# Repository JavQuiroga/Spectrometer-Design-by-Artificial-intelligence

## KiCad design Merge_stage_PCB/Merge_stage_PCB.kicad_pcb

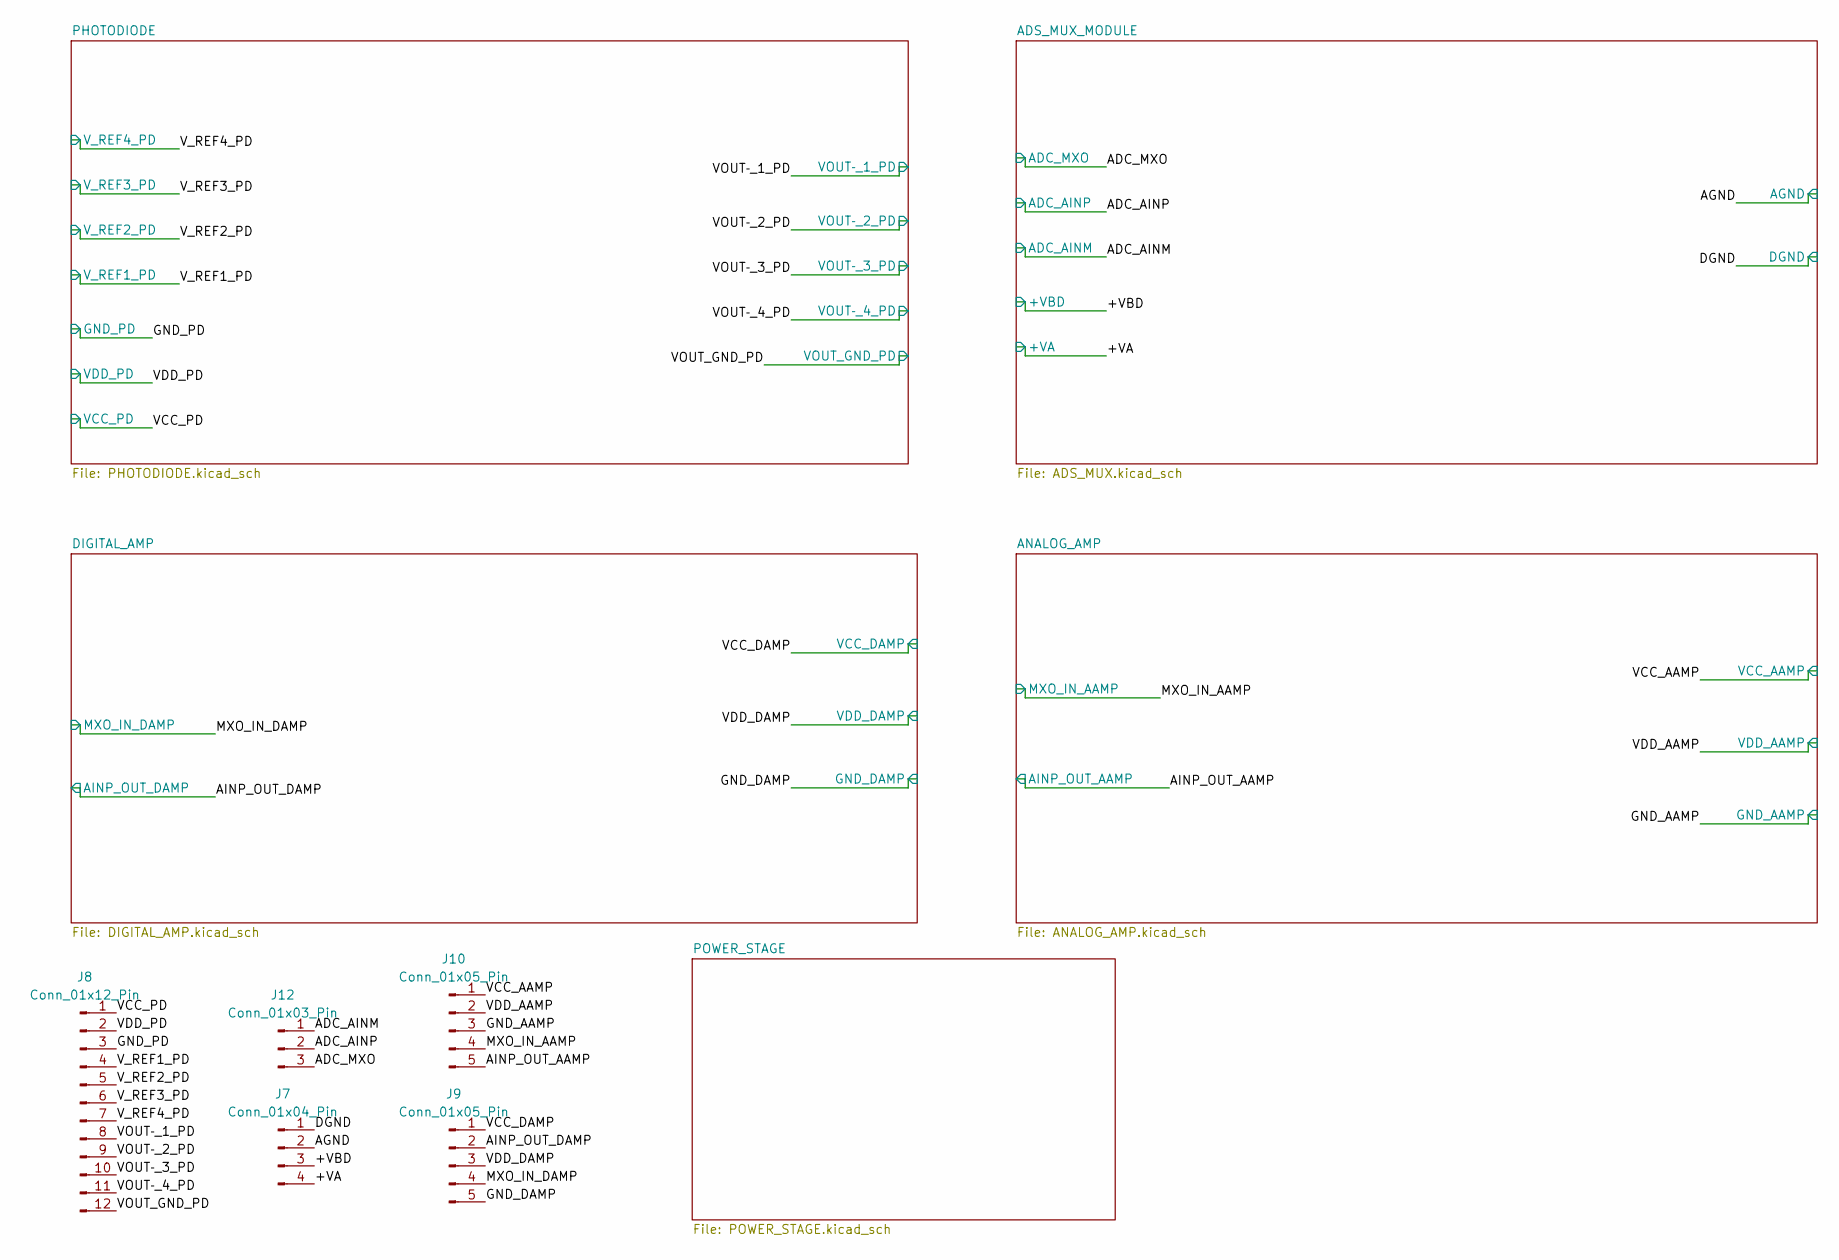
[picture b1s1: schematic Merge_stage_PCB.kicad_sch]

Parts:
J7: Conn_01x04_Pin; PinHeader_1x04_P2.54mm_Vertical
J8: Conn_01x12_Pin; PinHeader_1x12_P2.54mm_Vertical
J9, J10: Conn_01x05_Pin; PinHeader_1x05_P2.54mm_Vertical
J12: Conn_01x03_Pin; PinHeader_1x03_P2.54mm_Vertical

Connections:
+3.3V: J7.3; also elsewhere on the board
+5V: J7.4; also elsewhere on the board
/ADC_AINM: J12.1; also elsewhere on the board
/ADC_AINP: J12.2; also elsewhere on the board
/ADC_MXO: J12.3; also elsewhere on the board
/AGND: J7.2; also elsewhere on the board
/AINP_OUT_AAMP: J10.5; also elsewhere on the board
/AINP_OUT_DAMP: J9.2; also elsewhere on the board
/DGND: J7.1; also elsewhere on the board
/MXO_IN_AAMP: J10.4; also elsewhere on the board
/MXO_IN_DAMP: J9.4; also elsewhere on the board
/VCC_AAMP: J10.1; also elsewhere on the board
/VCC_DAMP: J9.1; also elsewhere on the board
/VCC_PD: J8.1; also elsewhere on the board
/VDD_AAMP: J10.2; also elsewhere on the board
/VDD_DAMP: J9.3; also elsewhere on the board
/VDD_PD: J8.2; also elsewhere on the board
/VOUT­_1_PD: J8.8; also elsewhere on the board
/VOUT­_2_PD: J8.9; also elsewhere on the board
/VOUT­_3_PD: J8.10; also elsewhere on the board
/VOUT­_4_PD: J8.11; also elsewhere on the board
/V_REF1_PD: J8.4; also elsewhere on the board
/V_REF2_PD: J8.5; also elsewhere on the board
/V_REF3_PD: J8.6; also elsewhere on the board
/V_REF4_PD: J8.7; also elsewhere on the board
GND_AAMP: J10.3; also elsewhere on the board
GND_DAMP: J9.5; also elsewhere on the board
GND_PD: J8.3, J8.12; also elsewhere on the board

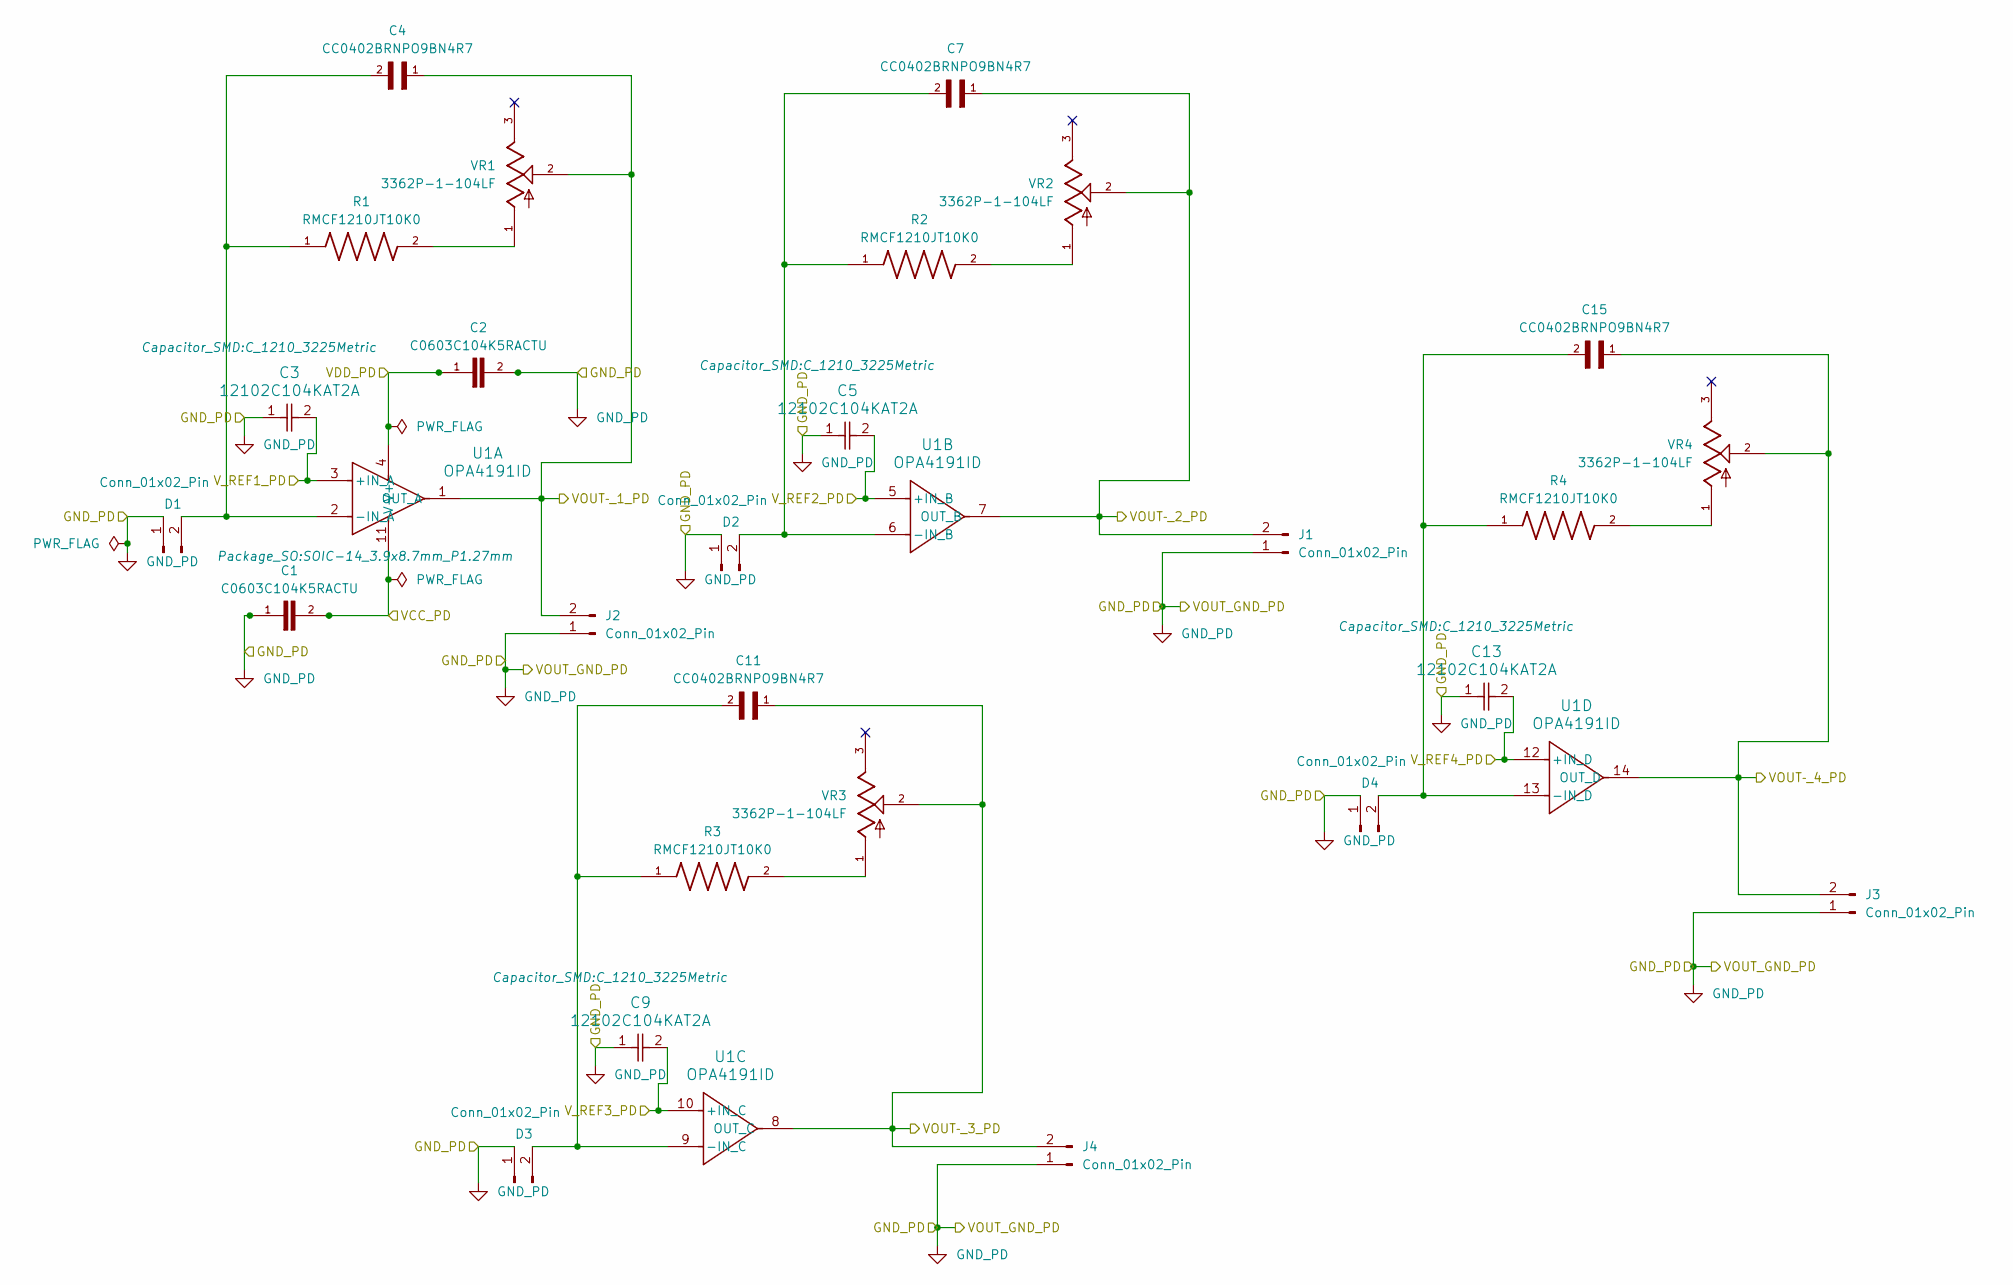
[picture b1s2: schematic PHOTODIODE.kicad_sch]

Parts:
C1, C2: C0603C104K5RACTU; C_0603_1608Metric
C3, C5, C9, C13: 12102C104KAT2A; C_1210_3225Metric
C4, C7, C15: CC0402BRNPO9BN4R7; C_0402_1005Metric
C11: CC0402BRNPO9BN4R7; C_0402_1005Metric_Pad0.74x0.62mm_HandSolder
D1, D2, D3, D4: Conn_01x02_Pin; PinHeader_1x02_P2.00mm_Vertical
J1, J2, J3, J4: Conn_01x02_Pin; PinHeader_1x02_P2.54mm_Vertical
R1, R2, R3, R4: RMCF1210JT10K0; R_1210_3225Metric
U1: OPA4191ID; SOIC-14_3.9x8.7mm_P1.27mm
VR1, VR2, VR3, VR4: 3362P-1-104LF; TRIM_3362P-1-104LF; PARTREV 08/26/10

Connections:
/VCC_PD: C1.2, U1.11 (V-); also elsewhere on the board
/VDD_PD: C2.1, U1.4 (V+); also elsewhere on the board
/VOUT­_1_PD: C4.1, J2.2, U1.1 (OUT_A), VR1.2; also elsewhere on the board
/VOUT­_2_PD: C7.1, J1.2, U1.7 (OUT_B), VR2.2; also elsewhere on the board
/VOUT­_3_PD: C11.1, J4.2, U1.8 (OUT_C), VR3.2; also elsewhere on the board
/VOUT­_4_PD: C15.1, J3.2, U1.14 (OUT_D), VR4.2; also elsewhere on the board
/V_REF1_PD: C3.2, U1.3 (+IN_A); also elsewhere on the board
/V_REF2_PD: C5.2, U1.5 (+IN_B); also elsewhere on the board
/V_REF3_PD: C9.2, U1.10 (+IN_C); also elsewhere on the board
/V_REF4_PD: C13.2, U1.12 (+IN_D); also elsewhere on the board
GND_PD: C1.1, C2.2, C3.1, C5.1, C9.1, C13.1, D1.1, D2.1, D3.1, D4.1, J1.1, J2.1, J3.1, J4.1; also elsewhere on the board
unnamed: C4.2, D1.2, R1.1, U1.2 (-IN_A)
unnamed: C7.2, D2.2, R2.1, U1.6 (-IN_B)
unnamed: C11.2, D3.2, R3.1, U1.9 (-IN_C)
unnamed: C15.2, D4.2, R4.1, U1.13 (-IN_D)
unnamed: R1.2, VR1.1
unnamed: R2.2, VR2.1
unnamed: R3.2, VR3.1
unnamed: R4.2, VR4.1

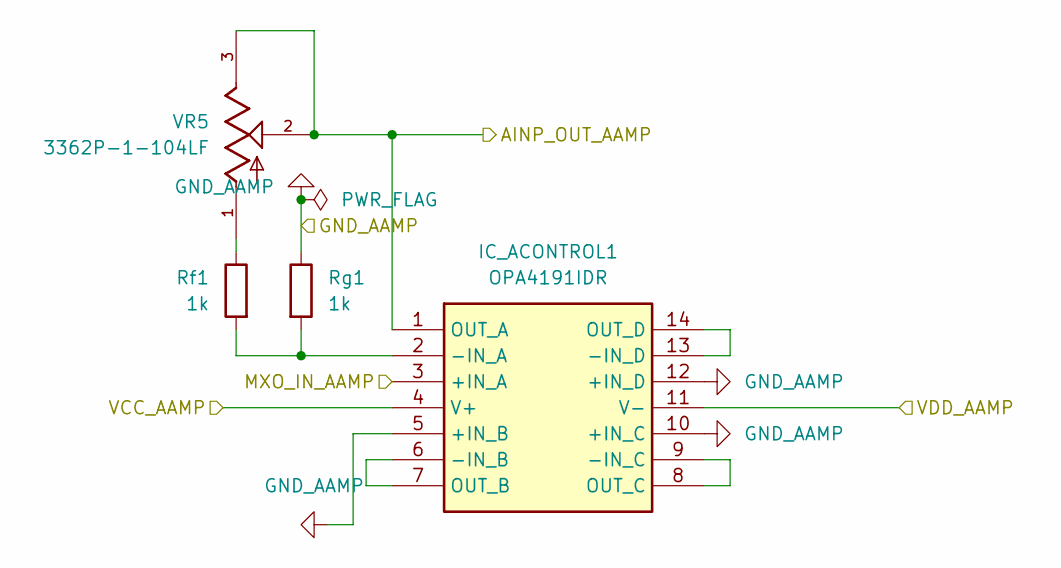
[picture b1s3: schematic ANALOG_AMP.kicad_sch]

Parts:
IC_ACONTROL1: OPA4191IDR; SOIC127P600X175-14N; Mouser Part Number 595-OPA4191IDR
Rf1: 1k; R_1210_3225Metric
Rg1: 1k; R_1210_3225Metric
VR5: 3362P-1-104LF; TRIM_3362P-1-104LF; PARTREV 08/26/10

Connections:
/AINP_OUT_AAMP: IC_ACONTROL1.1 (OUT_A), VR5.2, VR5.3; also elsewhere on the board
GND_AAMP: IC_ACONTROL1.5 (+IN_B), IC_ACONTROL1.10 (+IN_C), IC_ACONTROL1.12 (+IN_D), Rg1.1; also elsewhere on the board
unnamed 65: IC_ACONTROL1.2 (-IN_A), Rf1.2, Rg1.2; also elsewhere on the board
unnamed: IC_ACONTROL1.6 (-IN_B), IC_ACONTROL1.7 (OUT_B)
unnamed: IC_ACONTROL1.8 (OUT_C), IC_ACONTROL1.9 (-IN_C)
unnamed: IC_ACONTROL1.13 (-IN_D), IC_ACONTROL1.14 (OUT_D)
unnamed: Rf1.1, VR5.1

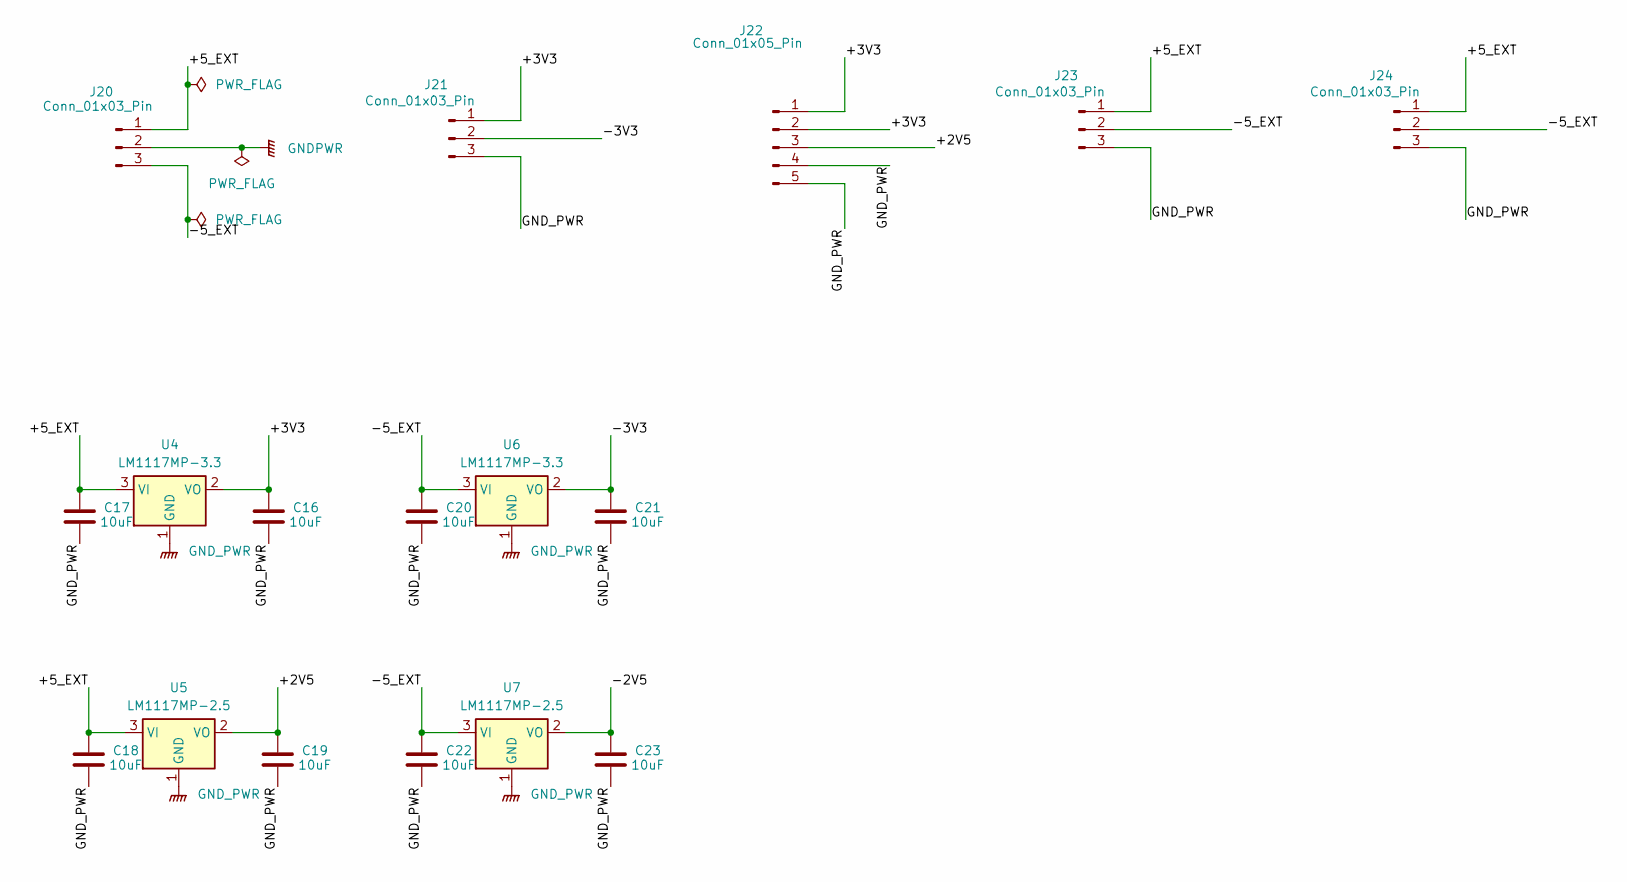
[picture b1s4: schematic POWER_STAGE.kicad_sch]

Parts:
C16, C17, C18, C19, C20, C21, C22, C23: 10uF; C_0805_2012Metric
J20, J21, J23, J24: Conn_01x03_Pin; PinHeader_1x03_P2.54mm_Vertical
J22: Conn_01x05_Pin; PinHeader_1x05_P2.54mm_Vertical
U4, U6: LM1117MP-3.3; SOT-223-3_TabPin2
U5, U7: LM1117MP-2.5; SOT-223-3_TabPin2

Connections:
/POWER_STAGE/+2V5: C19.1, J22.3, U5.2 (VO)
/POWER_STAGE/+3V3: C16.1, J21.1, J22.1, J22.2, U4.2 (VO)
/POWER_STAGE/+5_EXT: C17.1, C18.1, J20.1, J23.1, J24.1, U4.3 (VI), U5.3 (VI)
/POWER_STAGE/-2V5: C23.1, U7.2 (VO)
/POWER_STAGE/-3V3: C21.1, J21.2, U6.2 (VO)
/POWER_STAGE/-5_EXT: C20.1, C22.1, J20.3, J23.2, J24.2, U6.3 (VI), U7.3 (VI)
GNDPWR: J20.2
GND_PWR: C16.2, C17.2, C18.2, C19.2, C20.2, C21.2, C22.2, C23.2, J21.3, J22.4, J22.5, J23.3, J24.3, U4.1 (GND), U5.1 (GND), U6.1 (GND), U7.1 (GND)

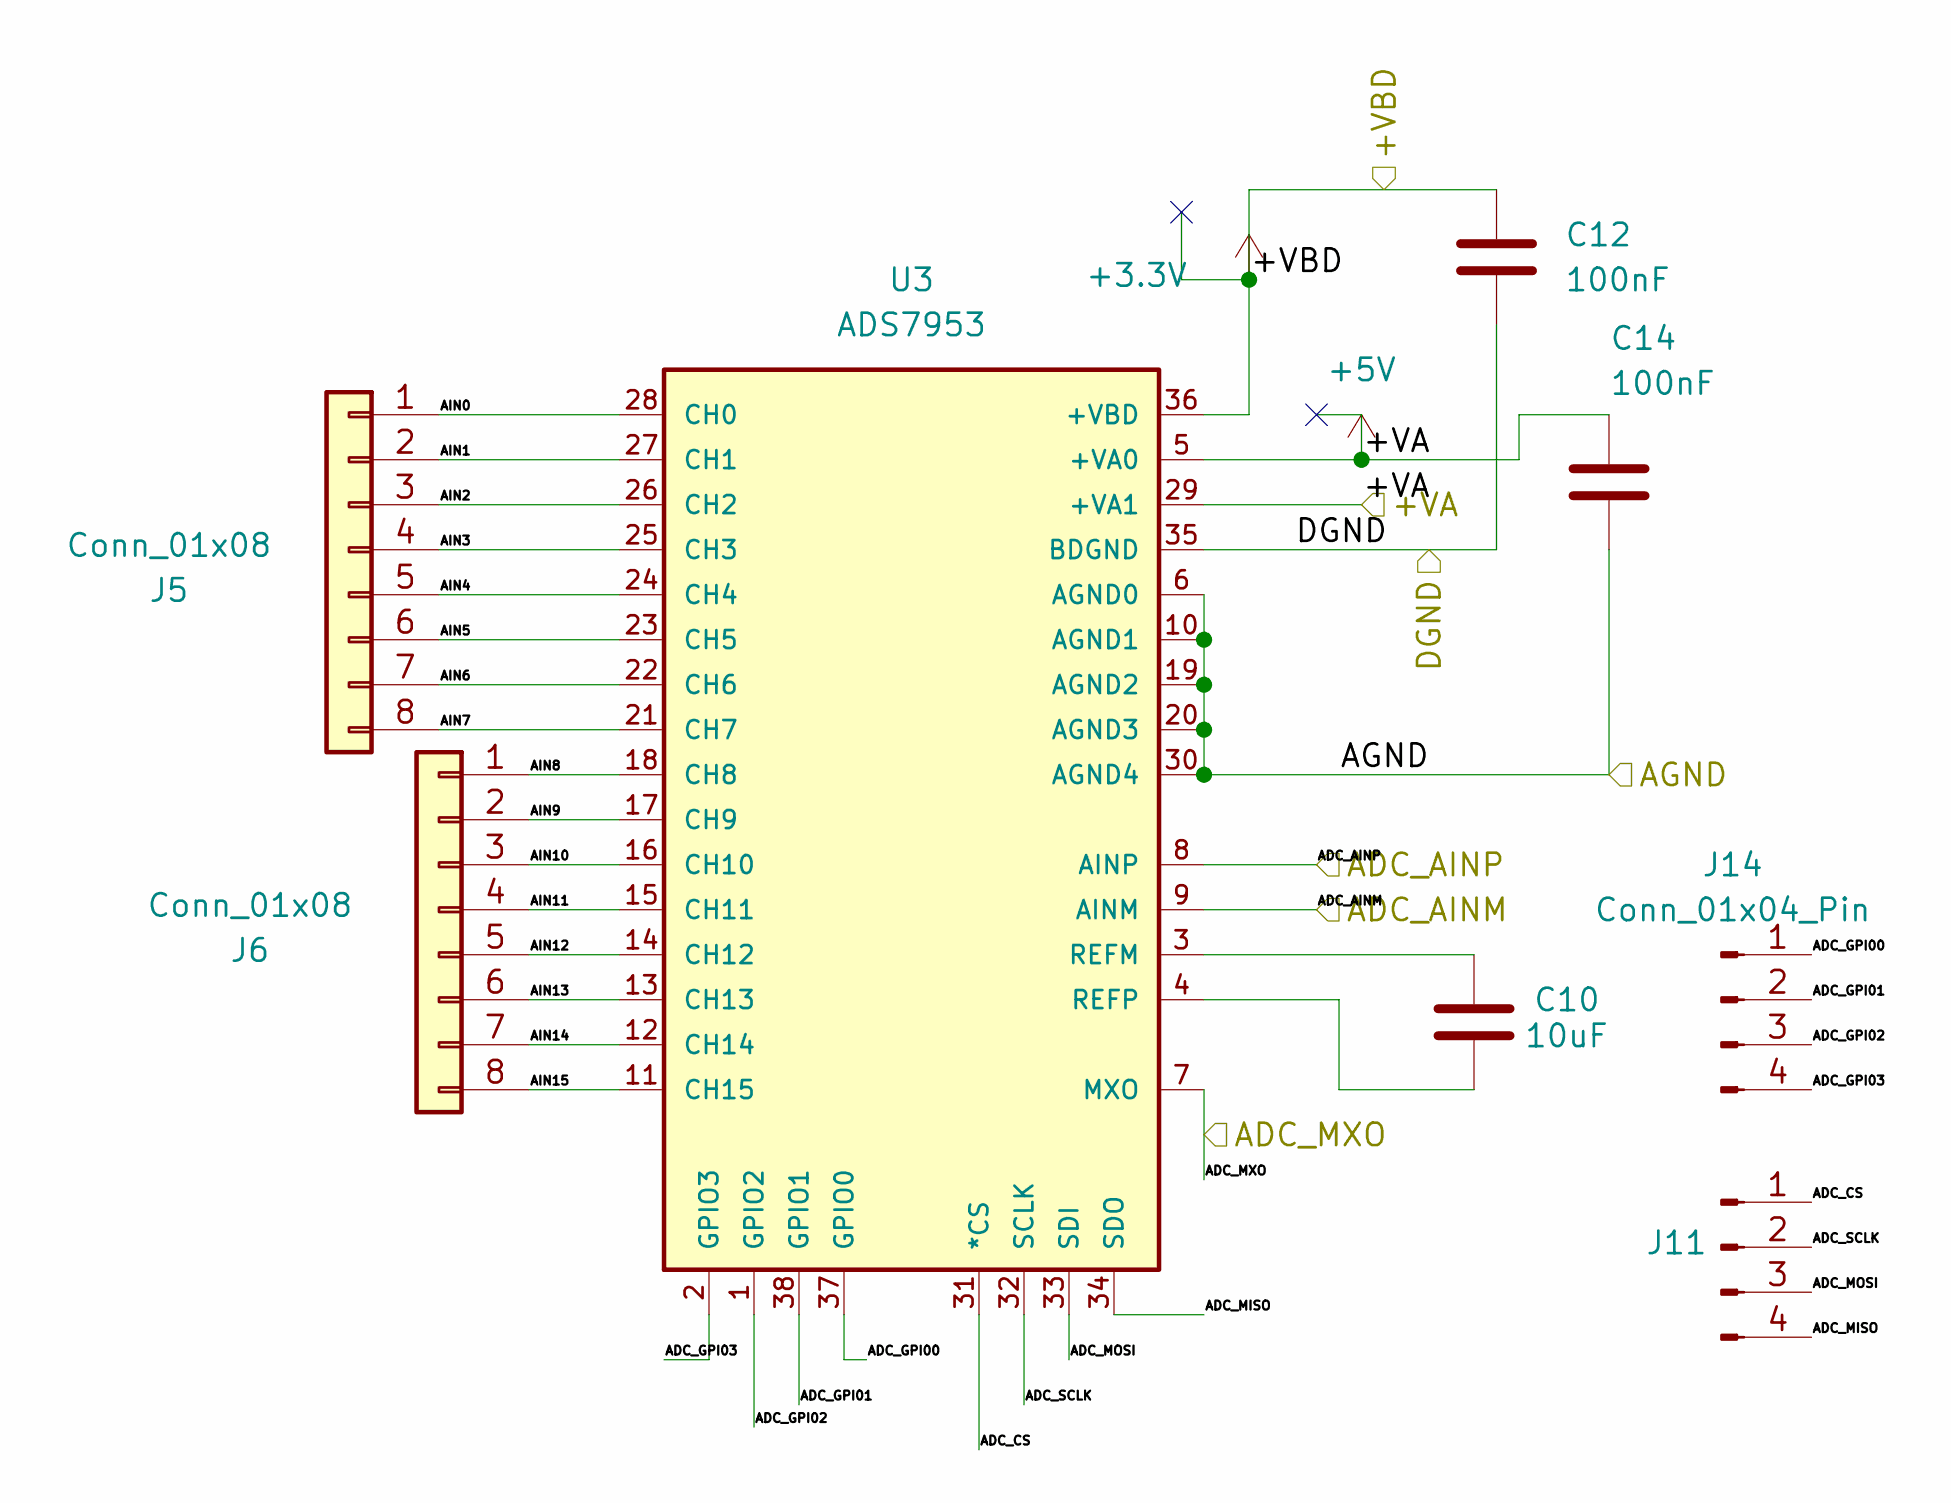
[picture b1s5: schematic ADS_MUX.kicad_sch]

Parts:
C10: 10uF; C_0805_2012Metric
C12, C14: 100nF; C_0805_2012Metric
J5, J6: Conn_01x08; PinHeader_1x08_P2.54mm_Vertical
J11, J14: Conn_01x04_Pin; PinHeader_1x04_P2.54mm_Vertical
U3: ADS7953

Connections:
+3.3V: C12.1, U3.36 (+VBD); also elsewhere on the board
+5V: C14.1, U3.5 (+VA0), U3.29 (+VA1); also elsewhere on the board
/ADC_AINM: U3.9 (AINM); also elsewhere on the board
/ADC_AINP: U3.8 (AINP); also elsewhere on the board
/ADC_MXO: U3.7 (MXO); also elsewhere on the board
/ADS_MUX_MODULE/ADC_CS: J11.1, U3.31 (*CS)
/ADS_MUX_MODULE/ADC_GPI00: J14.1, U3.37 (GPIO0)
/ADS_MUX_MODULE/ADC_GPI01: J14.2, U3.38 (GPIO1)
/ADS_MUX_MODULE/ADC_GPI02: J14.3, U3.1 (GPIO2)
/ADS_MUX_MODULE/ADC_GPI03: J14.4, U3.2 (GPIO3)
/ADS_MUX_MODULE/ADC_MISO: J11.4, U3.34 (SDO)
/ADS_MUX_MODULE/ADC_MOSI: J11.3, U3.33 (SDI)
/ADS_MUX_MODULE/ADC_SCLK: J11.2, U3.32 (SCLK)
/ADS_MUX_MODULE/AIN0: J5.1, U3.28 (CH0)
/ADS_MUX_MODULE/AIN1: J5.2, U3.27 (CH1)
/ADS_MUX_MODULE/AIN2: J5.3, U3.26 (CH2)
/ADS_MUX_MODULE/AIN3: J5.4, U3.25 (CH3)
/ADS_MUX_MODULE/AIN4: J5.5, U3.24 (CH4)
/ADS_MUX_MODULE/AIN5: J5.6, U3.23 (CH5)
/ADS_MUX_MODULE/AIN6: J5.7, U3.22 (CH6)
/ADS_MUX_MODULE/AIN7: J5.8, U3.21 (CH7)
/ADS_MUX_MODULE/AIN8: J6.1, U3.18 (CH8)
/ADS_MUX_MODULE/AIN9: J6.2, U3.17 (CH9)
/ADS_MUX_MODULE/AIN10: J6.3, U3.16 (CH10)
/ADS_MUX_MODULE/AIN11: J6.4, U3.15 (CH11)
/ADS_MUX_MODULE/AIN12: J6.5, U3.14 (CH12)
/ADS_MUX_MODULE/AIN13: J6.6, U3.13 (CH13)
/ADS_MUX_MODULE/AIN14: J6.7, U3.12 (CH14)
/ADS_MUX_MODULE/AIN15: J6.8, U3.11 (CH15)
/AGND: C14.2, U3.6 (AGND0), U3.10 (AGND1), U3.19 (AGND2), U3.20 (AGND3), U3.30 (AGND4); also elsewhere on the board
/DGND: C12.2, U3.35 (BDGND); also elsewhere on the board
/VREF_ADC: C10.2, U3.4 (REFP)
unnamed: C10.1, U3.3 (REFM)

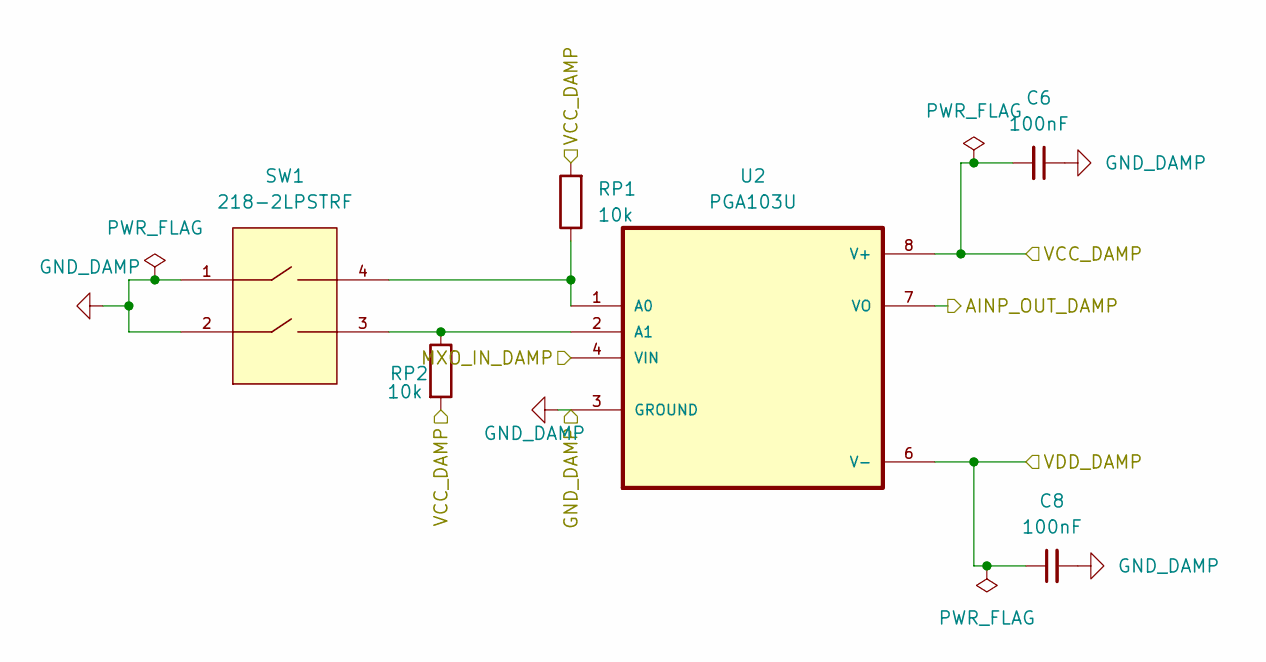
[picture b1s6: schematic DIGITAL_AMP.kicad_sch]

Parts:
C6, C8: 100nF; C_1210_3225Metric
RP1, RP2: 10k; R_1210_3225Metric
SW1: 218-2LPSTRF; SW_218-2LPSTRF; MPN 218-2LPSTRF
U2: PGA103U; SOIC127P599X175-8N

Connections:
/VCC_DAMP: C6.2, RP1.2, RP2.2, U2.8 (V+); also elsewhere on the board
/VDD_DAMP: C8.1, U2.6 (V-); also elsewhere on the board
GND_DAMP: C6.1, C8.2, SW1.1, SW1.2, U2.3 (GROUND); also elsewhere on the board
unnamed 77: RP1.1, SW1.4, U2.1 (A0); also elsewhere on the board
unnamed 78: RP2.1, SW1.3, U2.2 (A1); also elsewhere on the board

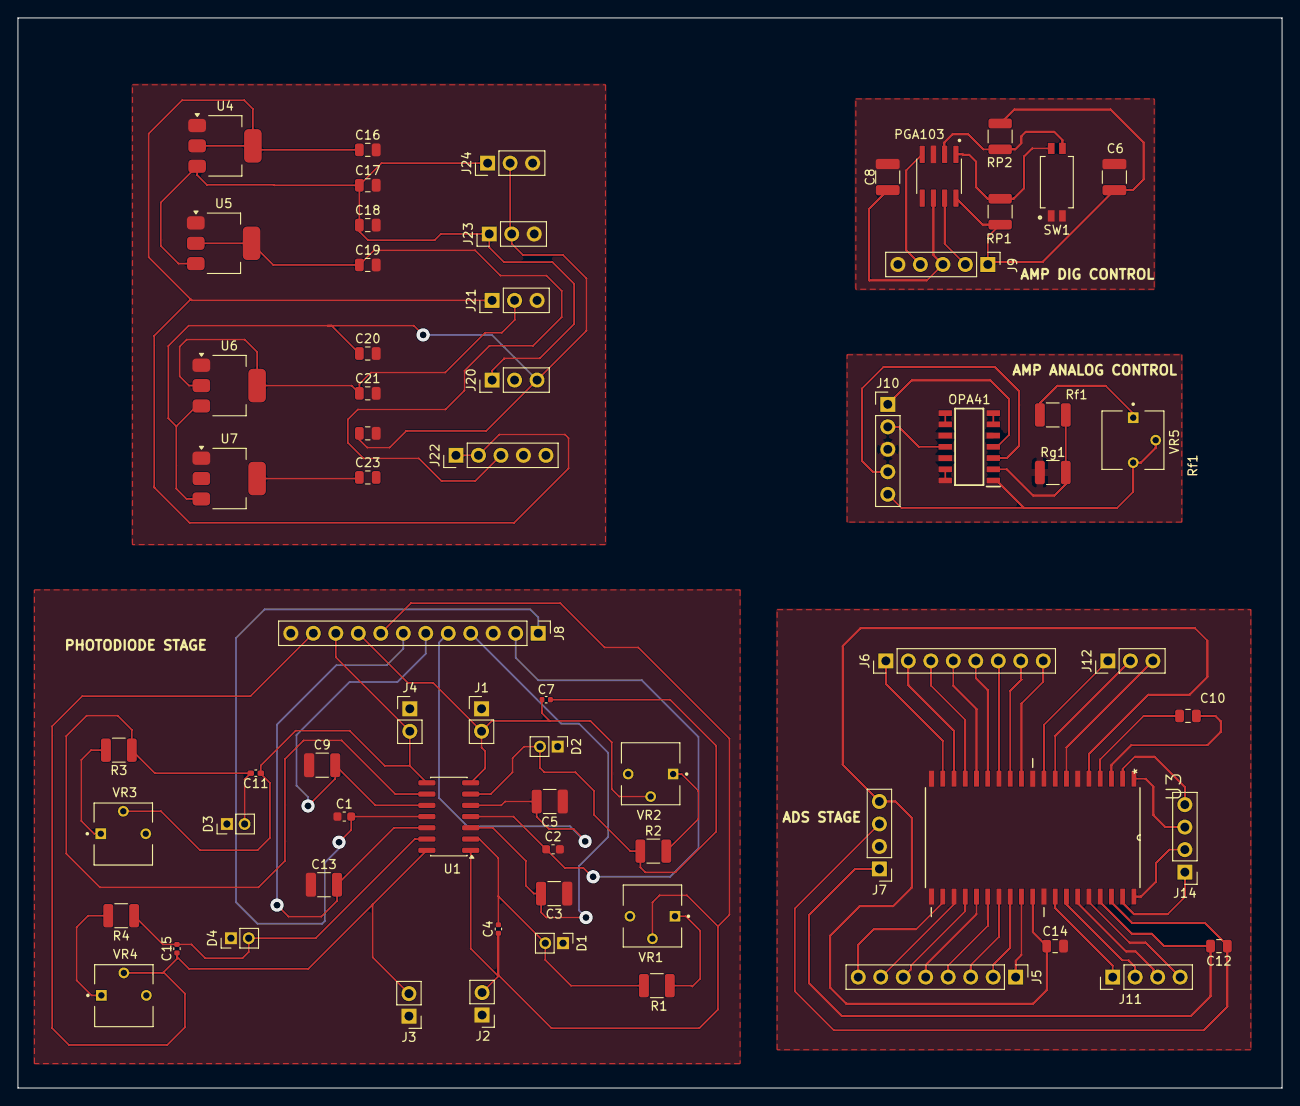
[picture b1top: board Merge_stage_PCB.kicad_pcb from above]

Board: 2 copper layers, 142.8 x 120.9 mm, 67 parts (0 on the bottom side), 76 nets.

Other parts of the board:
AMP ANALOG CONTROL: OPA4191IDR; SOIC127P600X175-14N
PGA103: PGA103U; SOIC127P599X175-8N

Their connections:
/AINP_OUT_AAMP: AMP ANALOG CONTROL.1 (OUT_A); also elsewhere on the board
/AINP_OUT_DAMP: PGA103.7 (VO); also elsewhere on the board
/MXO_IN_AAMP: AMP ANALOG CONTROL.3 (+IN_A); also elsewhere on the board
/MXO_IN_DAMP: PGA103.4 (VIN); also elsewhere on the board
/VCC_AAMP: AMP ANALOG CONTROL.4 (V+); also elsewhere on the board
/VCC_DAMP: PGA103.8 (V+); also elsewhere on the board
/VDD_AAMP: AMP ANALOG CONTROL.11 (V-); also elsewhere on the board
/VDD_DAMP: PGA103.6 (V-); also elsewhere on the board
GND_AAMP: AMP ANALOG CONTROL.5 (+IN_B), AMP ANALOG CONTROL.10 (+IN_C), AMP ANALOG CONTROL.12 (+IN_D); also elsewhere on the board
GND_DAMP: PGA103.3 (GROUND); also elsewhere on the board
unnamed 65: AMP ANALOG CONTROL.2 (-IN_A); also elsewhere on the board
unnamed: AMP ANALOG CONTROL.6 (-IN_B), AMP ANALOG CONTROL.7 (OUT_B)
unnamed: AMP ANALOG CONTROL.8 (OUT_C), AMP ANALOG CONTROL.9 (-IN_C)
unnamed: AMP ANALOG CONTROL.13 (-IN_D), AMP ANALOG CONTROL.14 (OUT_D)
unnamed 77: PGA103.1 (A0); also elsewhere on the board
unnamed 78: PGA103.2 (A1); also elsewhere on the board

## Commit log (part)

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2026-06-03 Todas las placas Routeadas
